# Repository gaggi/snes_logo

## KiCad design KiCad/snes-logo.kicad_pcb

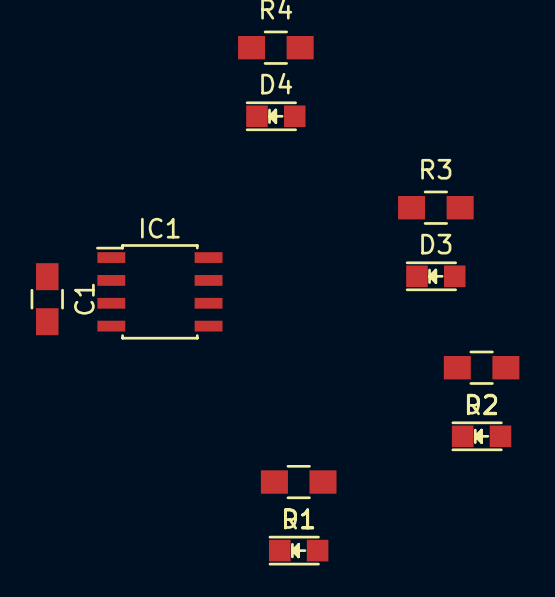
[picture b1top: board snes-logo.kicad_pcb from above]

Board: 2 copper layers, 10 parts (0 on the bottom side), 9 nets, no tracks yet.

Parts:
C1: 100µF; C_0805_HandSoldering
D1, D2, D3, D4: LED; LED-0805
IC1: ATTINY45-S; SOIC-8_3.9x4.9mm_Pitch1.27mm
R1, R2, R3, R4: R; R_0805_HandSoldering

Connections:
GND: C1.2, IC1.4, R1.2, R2.2, R3.2, R4.2
unnamed: D1.1, R1.1
unnamed: D2.1, R2.1
unnamed: D2.2, IC1.6
unnamed: D3.1, R3.1
unnamed: D3.2, IC1.7
unnamed: D4.1, R4.1
unnamed: D4.2, IC1.2
VCC: C1.1, IC1.8

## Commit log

2017-09-06 Added KiCad files
